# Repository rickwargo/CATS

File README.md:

#   C.A.T.S. 

## TODO
 - Module dependencies
 - Events
   - Event mapping that resides in systemSetup
   - Event dispatch that can deal with propagation 

### Enhancements
 - WiFi first then WiFiMulti to improve startup time
 - Pass different data based on event type
#### Done
 * [✓] Dynamically load and unload modules (low)

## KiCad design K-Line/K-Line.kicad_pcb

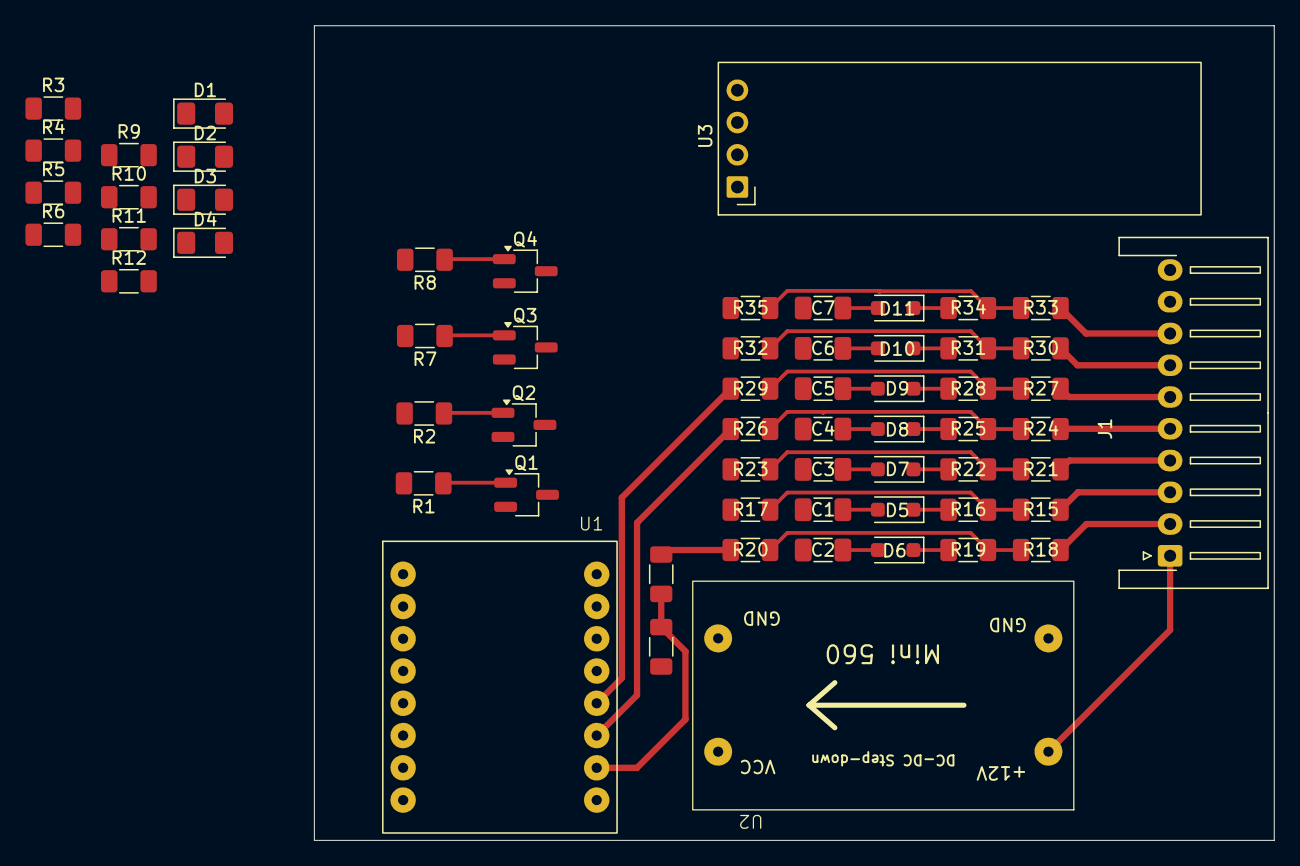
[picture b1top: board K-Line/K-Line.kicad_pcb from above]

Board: 2 copper layers, 75.6 x 64.1 mm, 61 parts (0 on the bottom side), 52 nets.

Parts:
C1, C2, C3, C4, C5, C6, C7: 100nF; C_1206_3216Metric_Pad1.33x1.80mm_HandSolder
D1, D3: Red LED; LED_1206_3216Metric_Pad1.42x1.75mm_HandSolder
D2, D4: LED; LED_1206_3216Metric_Pad1.42x1.75mm_HandSolder
D5, D6, D7, D8, D9, D10, D11: 3V3 0.5W; D_SOD-123F
J1: Conn_01x10_Pin; JST_XH_S10B-XH-A-1_1x10_P2.50mm_Horizontal
Q1, Q2, Q3, Q4: Q_NMOS_GSD; SC-59_Handsoldering
R1, R2, R7, R8: 100R; R_1206_3216Metric_Pad1.30x1.75mm_HandSolder
R3, R9: 220R; R_1206_3216Metric_Pad1.30x1.75mm_HandSolder
R4, R10: 510R; R_1206_3216Metric_Pad1.30x1.75mm_HandSolder
R5, R11, R14: 1K; R_1206_3216Metric_Pad1.30x1.75mm_HandSolder
R6, R12, R15, R16, R18, R19, R21, R22, R24, R25, R27, R28, R30, R31, R33, R34: 10K; R_1206_3216Metric_Pad1.30x1.75mm_HandSolder
R13: 4.7K; R_1206_3216Metric_Pad1.30x1.75mm_HandSolder
R17, R20, R23, R26, R29, R32, R35: 3K3; R_1206_3216Metric_Pad1.30x1.75mm_HandSolder
U1: ESP32-C3 SuperMini; ESP32-C3-SuperMini
U2: Mini-560
U3: ER_OLEDM0.91_1x-I2C

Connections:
+3V3: U2.4 (VCC), U3.2 (VCC)
+12V: J1.1, R4.1, R6.1, R10.1, R12.1, U2.1 (+12V)
/+12V SWITCHED: R13.2, R20.2
/+12V Switched Input/+12V_INPUT: J1.2, R18.1
/BRAKE: R29.2, U1.3 (GPIO7/SS)
/Brake Input/+12V_INPUT: J1.6, R27.1
/CLUTCH: R35.2, U1.6 (GPIO10)
/Clutch Input/+12V_INPUT: J1.8, R33.1
/HANDBRAKE: R26.2, U1.2 (GPIO6/MOSI)
/Handbrake Input/+12V_INPUT: J1.5, R24.1
/I2C_SCL: U1.8 (GPIO21/TX), U3.3 (SCL)
/I2C_SDA: U1.7 (GPIO20/RX), U3.4 (SDA)
/K-BUS: Q3.3 (D), Q4.3 (D), R10.2, R11.2, R12.2, R23.2
/K-BUS_RXD: R8.2, R9.2, U1.9 (A00)
/K-BUS_TXD: R7.2, U1.10 (A01)
/K-Bus Input/+12V_INPUT: J1.4, R21.1
/K-LINE: Q1.3 (D), Q2.3 (D), R4.2, R5.2, R6.2, R17.2
/K-LINE_RXD: R2.2, R3.2
/K-Line Input/+12V_INPUT: J1.3, R15.1
/PWR_MON: R13.1, R14.2, U1.1 (A05/MISO)
/REVERSE: R32.2, U1.5 (GPIO9/SCL)
/Reverse Input/+12V_INPUT: J1.7, R30.1
GND: C1.2, C2.2, C3.2, C4.2, C5.2, C6.2, C7.2, D1.1 (K), D2.1 (K), D3.1 (K), D4.1 (K), J1.10, Q1.2 (S), Q2.2 (S), Q3.2 (S), Q4.2 (S), R14.1, U2.2 (GNDPWR), U2.3 (GND), U3.1 (GND)
unnamed: D1.2 (A), R3.1
unnamed: D2.2 (A), R5.1
unnamed: D3.2 (A), R9.1
unnamed: D4.2 (A), R11.1
unnamed: C1.1, D5.2 (A)
unnamed: D5.1 (K), R16.2
unnamed: C2.1, D6.2 (A)
unnamed: D6.1 (K), R19.2
unnamed: C3.1, D7.2 (A)
unnamed: D7.1 (K), R22.2
unnamed: C4.1, D8.2 (A)
unnamed: D8.1 (K), R25.2
unnamed: C5.1, D9.2 (A)
unnamed: D9.1 (K), R28.2
unnamed: C6.1, D10.2 (A)
unnamed: D10.1 (K), R31.2
unnamed: C7.1, D11.2 (A)
unnamed: D11.1 (K), R34.2
unnamed: Q1.1 (G), R1.1
unnamed: Q2.1 (G), R2.1
unnamed: Q3.1 (G), R7.1
unnamed: Q4.1 (G), R8.1
unnamed: R15.2, R16.1, R17.1
unnamed: R18.2, R19.1, R20.1
unnamed: R21.2, R22.1, R23.1
unnamed: R24.2, R25.1, R26.1
unnamed: R27.2, R28.1, R29.1
unnamed: R30.2, R31.1, R32.1
unnamed: R33.2, R34.1, R35.1

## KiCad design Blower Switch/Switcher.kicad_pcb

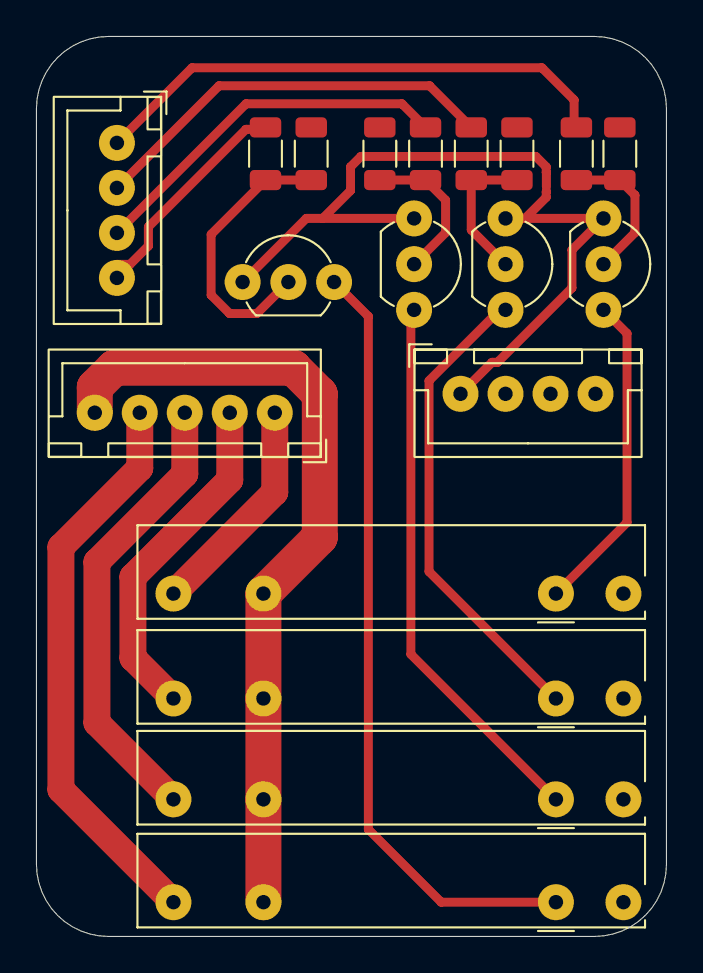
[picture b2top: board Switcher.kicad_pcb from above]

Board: 2 copper layers, 35.0 x 50.0 mm, 19 parts (0 on the bottom side), 19 nets.

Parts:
J1: Conn_01x04_Socket; JST_XH_B5B-XH-A_1x05_P2.50mm_Vertical
Q1, Q2, Q3, Q4: BC337; TO-92_Inline_Wide
R1, R2, R3, R4: 100K; R_1206_3216Metric
R5, R6, R7, R8: 2K2; R_1206_3216Metric
U1, U2, U3, U4: 34.81-7048; Finder_34.81
U5: GPIO Block; JST_XH_B4B-XH-A_1x04_P2.50mm_Vertical
U6: 3.3V Power; JST_XH_B4B-XH-A_1x04_P2.50mm_Vertical

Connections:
+3V3: Q1.1 (C), Q2.1 (C), Q3.1 (C), Q4.1 (C), U6.1 (3V3)
+12V: J1.5, U1.11, U2.11, U3.11, U4.11
/GPIO2: R5.1, U5.1 (GPIO2)
/GPIO3: R6.1, U5.2 (GPIO3)
/GPIO4: R7.1, U5.3 (GPIO4)
/GPIO21: R8.1, U5.4 (GPIO21)
/Select Speed 1: Q1.3 (E), U1.A1
/Select Speed 2: Q2.3 (E), U2.A1
/Select Speed 3: Q3.3 (E), U3.A1
/Select Speed 4: Q4.3 (E), U4.A1
/Speed 1: J1.1, U1.14
/Speed 1 Control: Q1.2 (B), R1.2, R5.2
/Speed 2: J1.2, U2.14
/Speed 2 Control: Q2.2 (B), R2.2, R6.2
/Speed 3: J1.3, U3.14
/Speed 3 Control: Q3.2 (B), R3.2, R7.2
/Speed 4: J1.4, U4.14
/Speed 4 Control: Q4.2 (B), R4.2, R8.2
GND: R1.1, R2.1, R3.1, R4.1, U1.A2, U2.A2, U3.A2, U4.A2, U6.2 (GND)

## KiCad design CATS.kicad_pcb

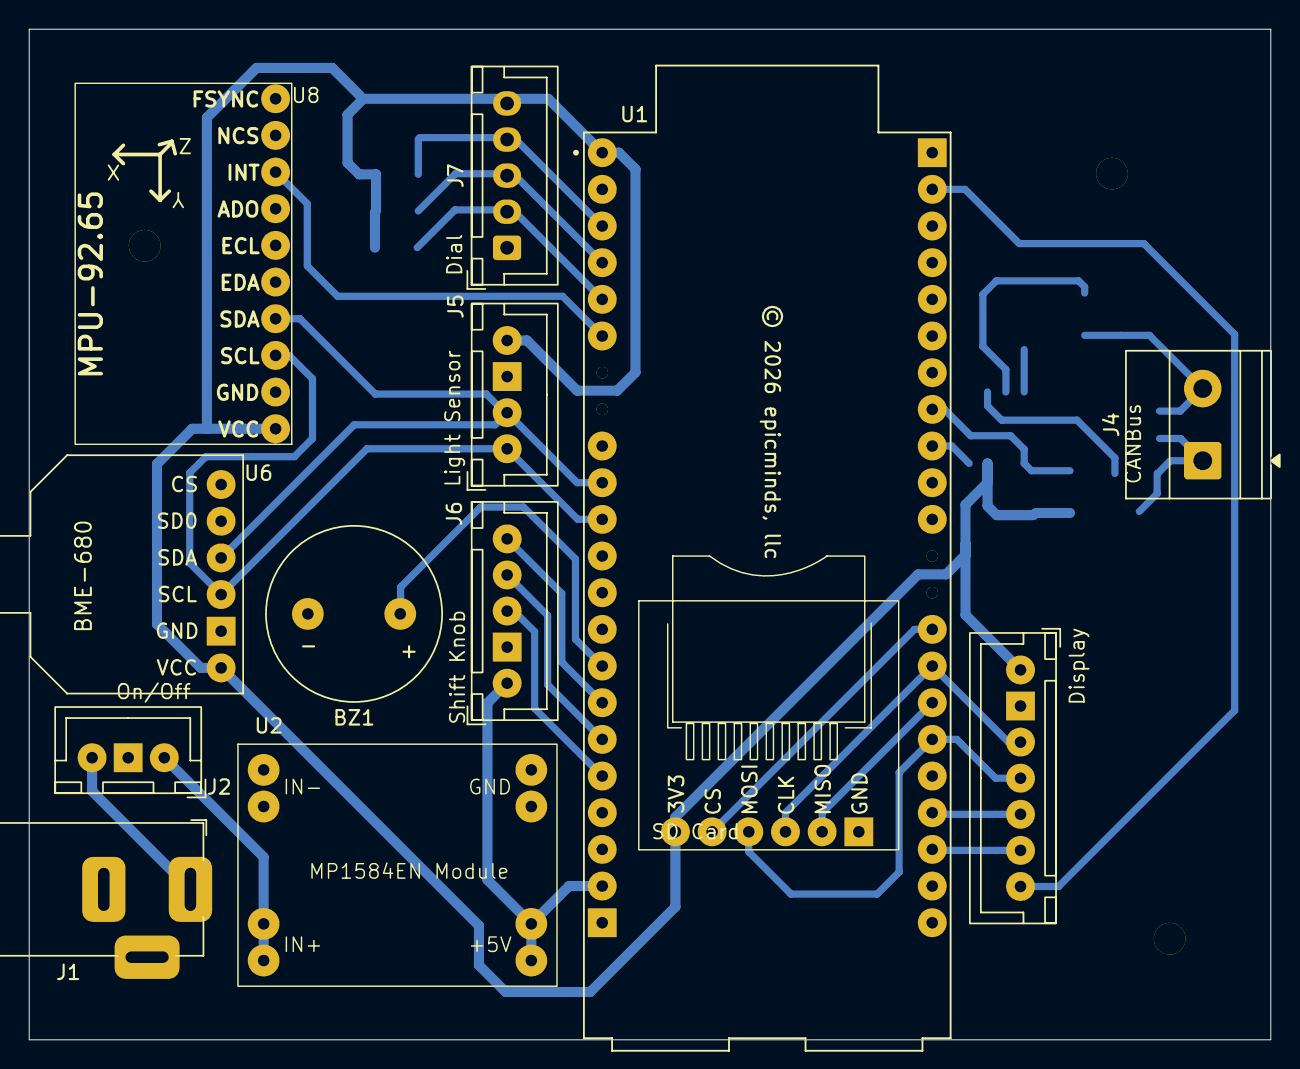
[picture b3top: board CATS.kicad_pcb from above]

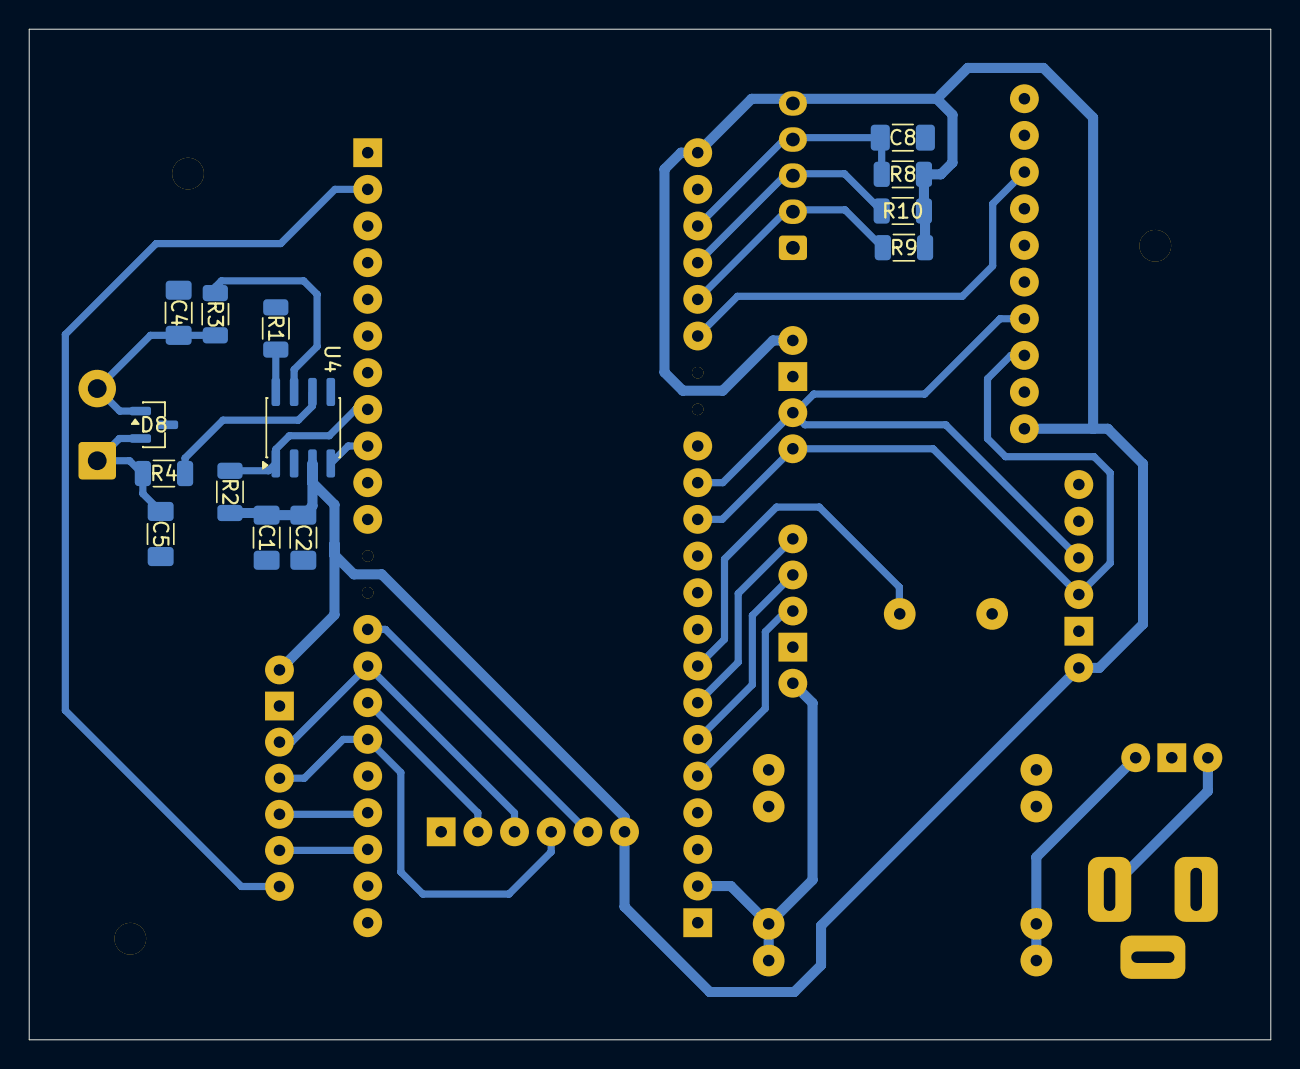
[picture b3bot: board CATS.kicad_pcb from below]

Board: 2 copper layers, 86.0 x 70.0 mm, 27 parts (14 on the bottom side), 29 nets.

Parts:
BZ1: Buzzer; Passive Buzzer
C1: 10uF; C_1206_3216Metric_Pad1.33x1.80mm_HandSolder
C2: 100nF; C_1206_3216Metric_Pad1.33x1.80mm_HandSolder
C4, C5: 47pF; C_1206_3216Metric_Pad1.33x1.80mm_HandSolder
C8: 0.1uF; C_1206_3216Metric_Pad1.33x1.80mm_HandSolder
D8: PESD5V0L2BT; SOT-23
J1: Barrel_Jack; BarrelJack_Horizontal
J2: Conn_01x03; JST_XH_B3B-XH-A_1x03_P2.50mm_Vertical
J3: Conn_01x07; JST_XH_B7B-XH-A_1x07_P2.50mm_Vertical
J4: Conn_01x02; TerminalBlock_Phoenix_MKDS-1,5-2_1x02_P5.00mm_Horizontal
J5: Conn_01x04; JST_XH_B4B-XH-A_1x04_P2.50mm_Vertical
J6, J7: Conn_01x05; JST_XH_B5B-XH-A_1x05_P2.50mm_Vertical
R1: 0R; R_1206_3216Metric
R2: 4K7; R_1206_3216Metric
R3, R4: 10R; R_1206_3216Metric
R8, R9, R10: 10K; R_1206_3216Metric
U1: ESP32-S3-DevKitM-1-N8
U2: MP1584EN; MP1584EN_DCDC_THT_Module
U4: SN65HVD230; SOIC-8_3.9x4.9mm_P1.27mm
U5: Micro_SD_Card
U6: BME-680
U8: MPU-6050; MPU-6500

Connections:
+3.3V: C1.1, C2.1, J3.1, J5.4, J7.5, R2.2, R8.1, R9.1, R10.1, U1.J1_1 (3V3), U4.3 (VCC), U5.1 (3V3), U6.1 (VCC), U8.1 (VCC)
+5V: J6.1, U1.J1_21 (5V0), U2.4 (VOUT)
+12V: J2.1, U2.1 (VIN)
/+12V_IN: J1.1 (+12V), J2.3
/CAN RS: R1.2, U4.8 (Rs)
/CANBUS+: R3.1, U4.7 (CANH)
/CANBUS-: R4.2, U4.6 (CANL)
/CB+EXT: C4.2, D8.1 (A1), J4.2, R3.2
/CB-EXT: C5.1, D8.2 (A2), J4.1, R4.1
BUTTON1: C8.1, J7.4, R8.2, U1.J1_3 (GPIO1)
BUZZER: BZ1.1 (+), U1.J1_15 (GPIO13)
CAN D: R2.1, U1.J3_8 (GPIO41), U4.1 (D)
CAN R: U1.J3_9 (GPIO40), U4.4 (R)
ENCODER A: J7.3, R10.2, U1.J1_4 (GPIO2)
ENCODER B: J7.2, R9.2, U1.J1_5 (GPIO3)
FSPI CLK: J3.3, U1.J3_15 (GPIO34), U5.4 (CLK)
FSPI MISO: U1.J3_16 (GPIO33), U5.5 (MISO)
FSPI MOSI: J3.4, U1.J3_17 (GPIO26), U5.3 (MOSI)
GND: BZ1.2 (-), C1.2, C2.2, C4.1, C5.2, C8.2, D8.3 (common), J1.2 (GND), J2.2, J3.2, J5.3, J6.2, J7.1, R1.1, U1.J1_22 (GND_J1_22), U1.J3_1 (GND_J3_1), U2.2 (GND), U2.3 (GND), U4.2 (GND), U5.6 (GND), U6.2 (GND), U8.2 (GND)
HAPTIC1: J6.5, U1.J1_16 (GPIO14)
HAPTIC2: J6.4, U1.J1_17 (GPIO15)
LIGHTS: J6.3, U1.J1_18 (GPIO16)
MPU INT: U1.J1_6 (GPIO4), U8.8 (INT)
RESET: J3.7, U1.J3_2 (RST)
SCL: J5.1, U1.J1_11 (GPIO9), U6.3 (SCL), U8.3 (SCL)
SD CS: U1.J3_14 (GPIO35), U5.2 (~CS)
SDA: J5.2, U1.J1_10 (GPIO8), U6.4 (SDA), U8.4 (SDA)
TFT CS: J3.6, U1.J3_20 (GPIO19)
TFT DC: J3.5, U1.J3_19 (GPIO20)

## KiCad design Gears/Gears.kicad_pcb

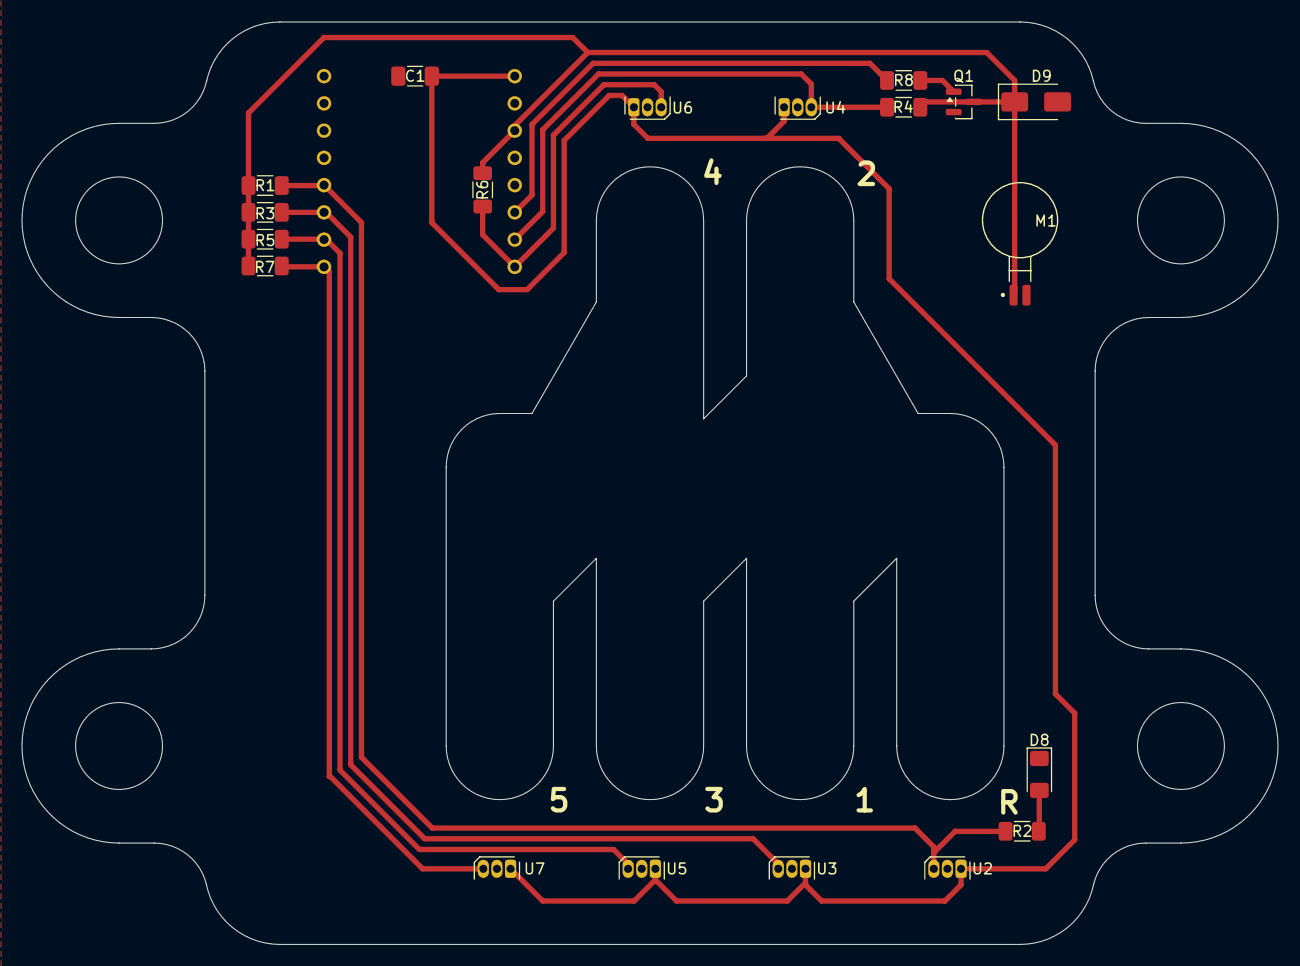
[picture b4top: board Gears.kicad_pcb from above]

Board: 2 copper layers, 117.1 x 86.0 mm, 20 parts (1 on the bottom side), 12 nets.

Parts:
C1: 0.1uF; C_1206_3216Metric_Pad1.33x1.80mm_HandSolder
D8: LED; LED_1206_3216Metric_Pad1.42x1.75mm_HandSolder
D9: SS12; D_SMA
M1: C0720B001F; XDCR_C0720B001F
Q1: BC817; SOT-23
R1, R3, R4, R5, R6, R7: 10K; R_1206_3216Metric_Pad1.30x1.75mm_HandSolder
R2: 220R; R_1206_3216Metric_Pad1.30x1.75mm_HandSolder
R8: 1K; R_1206_3216Metric_Pad1.30x1.75mm_HandSolder
U1: ESP32-C3-OLED; MODULE_ESP32-C3_OLED
U2, U3, U4, U5, U6, U7: A3314; TO-92S

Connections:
1ST_GEAR: R3.1, U1.5 (GPIO5), U3.3 (V_{OUT})
2ND_GEAR: R4.1, U1.1 (GPIO1), U4.3 (V_{OUT})
3RD_GEAR: R5.1, U1.4 (GPIO4), U5.3 (V_{OUT})
4TH_GEAR: R6.1, U1.0 (GPIO0), U6.3 (V_{OUT})
5TH_GEAR: R7.1, U1.3 (GPIO3), U7.3 (V_{OUT})
+3.3V: D9.1 (K), M1.1 (V+), Q1.3 (C), R1.1, R3.2, R4.2, R5.2, R6.2, R7.2, U1.3.3 (3V3)
+5V: C1.1, U1.5V, U2.1 (V_{CC}), U3.1 (V_{CC}), U4.1 (V_{CC}), U5.1 (V_{CC}), U6.1 (V_{CC}), U7.1 (V_{CC})
GND: C1.2, D8.1 (K), D9.2 (A), M1.2 (V-), Q1.2 (E), U1.G (GND), U2.2 (GND), U3.2 (GND), U4.2 (GND), U5.2 (GND), U6.2 (GND), U7.2 (GND)
HAPTIC: R8.1, U1.2 (GPIO2)
Haptic_Trigger: Q1.1 (B), R8.2
REVERSE: R1.2, R2.2, U1.6 (GPIO6), U2.3 (V_{OUT})
Reverse_Light: D8.2 (A), R2.1

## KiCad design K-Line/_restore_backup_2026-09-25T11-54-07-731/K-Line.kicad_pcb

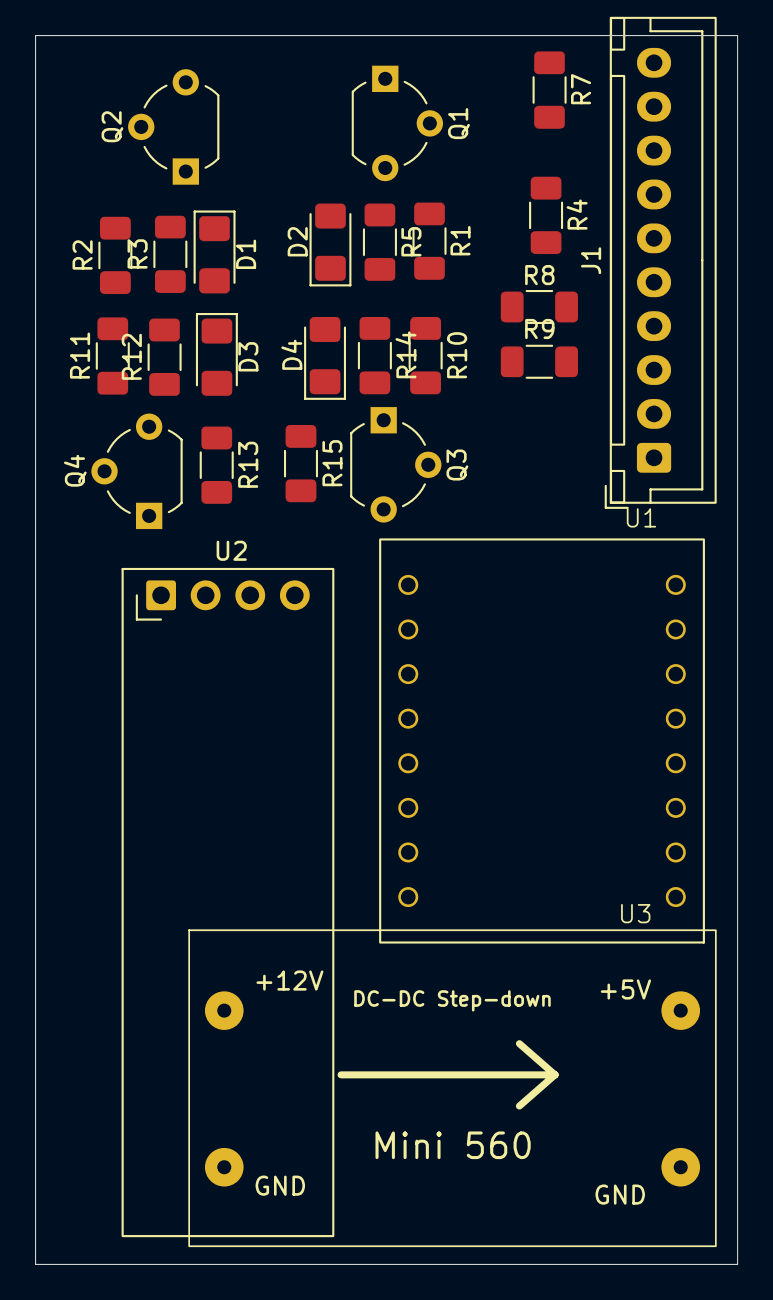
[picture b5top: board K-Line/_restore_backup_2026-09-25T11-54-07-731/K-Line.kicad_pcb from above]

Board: 2 copper layers, 40.0 x 70.0 mm, 26 parts (0 on the bottom side), 23 nets, no tracks yet.

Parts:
D1, D3: Red LED; LED_1206_3216Metric_Pad1.42x1.75mm_HandSolder
D2, D4: LED; LED_1206_3216Metric_Pad1.42x1.75mm_HandSolder
J1: Conn_01x10_Pin; JST_XH_B10B-XH-A_1x10_P2.50mm_Vertical
Q1, Q2, Q3, Q4: BC547; TO-92_Wide
R1, R2, R5, R9, R10, R11, R14: 1K; R_1206_3216Metric_Pad1.30x1.75mm_HandSolder
R3, R12: 220R; R_1206_3216Metric_Pad1.30x1.75mm_HandSolder
R4, R13: 510R; R_1206_3216Metric_Pad1.30x1.75mm_HandSolder
R7, R15: 10K; R_1206_3216Metric_Pad1.30x1.75mm_HandSolder
R8: 4.7K; R_1206_3216Metric_Pad1.30x1.75mm_HandSolder
U1: ESP32-C3 SuperMini; ESP32-C3-SuperMini
U2: ER_OLEDM0.91_1x-I2C
U3: Mini-560

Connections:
+3V3: U2.2 (VCC), U3.4 (VCC)
+12V: J1.1, R4.1, R7.1, R13.1, R15.1, U3.1 (+12V)
/+12V SWITCHED: J1.2, R8.2
/BRAKE: J1.6, U1.3 (GPIO7/SS)
/CLUTCH: J1.8, U1.6 (GPIO10)
/HANDBRAKE: J1.5, U1.2 (GPIO6/MOSI)
/I2C_SCL: U1.8 (GPIO21/TX), U2.3 (SCL)
/I2C_SDA: U1.7 (GPIO20/RX), U2.4 (SDA)
/K-BUS: J1.4, Q3.1 (C), Q4.1 (C), R13.2, R14.2, R15.2
/K-BUS_RXD: R11.2, R12.2, U1.10 (A01)
/K-LINE: J1.3, Q1.1 (C), Q2.1 (C), R4.2, R5.2, R7.2
/K-LINE_RXD: R2.2, R3.2
/PWR_MON: R8.1, R9.2, U1.1 (A05/MISO)
/REVERSE: J1.7, U1.5 (GPIO9/SCL)
GND: D1.1 (K), D2.1 (K), D3.1 (K), D4.1 (K), J1.10, Q1.3 (E), Q2.3 (E), Q3.3 (E), Q4.3 (E), R9.1, U2.1 (GND), U3.2 (GNDPWR), U3.3 (GND)
unnamed: D1.2 (A), R3.1
unnamed: D2.2 (A), R5.1
unnamed: D3.2 (A), R12.1
unnamed: D4.2 (A), R14.1
unnamed: Q1.2 (B), R1.1
unnamed: Q2.2 (B), R2.1
unnamed: Q3.2 (B), R10.1
unnamed: Q4.2 (B), R11.1

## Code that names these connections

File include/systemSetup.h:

#pragma once

#define SHIFTER_UPDATES_PER_SECOND  30

#define VSPI_CLK                    2
#define VSPI_MISO                   4
#define VSPI_MOSI                   16
#define VSPI_FREQUENCY              10000000

#define VSPI_TFT_CS                 14
#define VSPI_TFT_DC                 27
#define VSPI_TFT_RST                12

#define FILE_BASE_NAME              "cats"
#define SD_CS                       15
#define SD_CLK                      VSPI_CLK
#define SD_MISO                     VSPI_MISO
#define SD_MOSI                     VSPI_MOSI

// #define IMU_INTERRUPT_PIN           19

#define ROTARY_BUTTON_PIN           36
#define ENCODER_A                   34 // Encoder CLK
#define ENCODER_B                   39 // Encoder DT
#define ENCODER_DEFAULT_STEPS       4

#define HAPTIC_PIN_1                32
#define HAPTIC_PIN_2                33
#define SHIFTER_PIN                 25

#define BUZZER_PIN                  17

#define CAN_TX_PIN                  ((gpio_num_t)5)
#define CAN_RX_PIN                  ((gpio_num_t)18)
#define CANBUS_SPEED                500

#define I2C_SDA                     22
#define I2C_SCL                     23
#define I2C_BUS_FREQUENCY           400000

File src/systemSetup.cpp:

#include "systemSetup.h"
#include "ModuleRegistry.h"

#include "SystemModule.h"
#ifdef UI_DISPLAY
#include "DisplayModule.h"
#endif
#ifdef NETWORKING
#include "NetworkModule.h"
#if defined(NETWORK_TIME)
#include "TimeModule.h"
#endif
#endif
#ifdef CANBUS
#include "CANBusModule.h"
#endif
#ifdef BUTTON
#include "ButtonModule.h"
#endif
#ifdef BUZZER_SOUND
#include "BuzzerModule.h"
#endif
#ifdef ENCODER
#include "EncoderModule.h"
#endif
#ifdef LIGHT_LEVEL_SENSOR
#include "LightLevelModule.h"
#endif
#if defined(SHIFTER_KNOB) && defined(HAPTIC)
#include "HapticModule.h"
#endif
#if defined(SHIFTER_KNOB) && (defined(HAPTIC) || defined(FAST_LED))
#include "ShifterModule.h"
#endif
#ifdef ENVIRONMENT_SENSOR
#include "EnvironmentModule.h"
#endif
#ifdef IMU_SENSOR
#include "IMUModule.h"
#endif
#ifdef STORAGE
#include "StorageModule.h"
#endif
#if defined(NETWORKING) && defined(OTA_UPDATE)
#include "OTAUpdateModule.h"
#endif

#ifdef UI_DISPLAY
#include "face/FaceManager.h"
#endif
#if defined(UI_DISPLAY) && defined(NETWORKING) && defined(NETWORK_TIME)
#include "face/ClockFace.h"
#endif
#if defined(UI_DISPLAY) && defined(ENVIRONMENT_SENSOR)
#include "face/TemperatureFace.h"
#include "face/HumidityFace.h"
#include "face/IAQFace.h"
#include "face/PressureFace.h"
#endif
#if defined(UI_DISPLAY) && defined(LIGHT_LEVEL_SENSOR)
#include "face/LightLevelFace.h"
#endif
#if defined(UI_DISPLAY) && defined(IMU_SENSOR)
#include "face/IMUFace.h"
#include "face/DGFace.h"
#include "face/AutoFace.h"
#endif
#if defined(UI_DISPLAY) && (defined(LIGHT_LEVEL_SENSOR) || defined(IMU_SENSOR) || defined(ENVIRONMENT_SENSOR))
#include "face/MeasuresFace.h"
#endif

void loadModules()
{
    ModuleRegistry& registry = ModuleRegistry::instance();

    // Load order is significant - specify dependent modules first
    static SystemModule systemModule("System Handler");
    registry.registerModule(systemModule);

#ifdef NETWORKING
    static NetworkModule networkModule("Network Overlord");
#if defined(NETWORK_TIME)
    static TimeModule timeModule("Time Syncer");
#endif
#if defined(NETWORKING) && defined(OTA_UPDATE)
    static OTAUpdateModule otaUpdateModule("OTA Updates");
#endif
#endif

#ifdef UI_DISPLAY
    static DisplayModule displayModule("Round Display");
    static FaceManager faceManager("Face Manager", 1000);   // Must be loaded prior to loading faces
#if defined(NETWORK_TIME)
    static ClockFace clockFace("Clock", 500);
#endif
#ifdef ENVIRONMENT_SENSOR
    static TemperatureFace temperatureFace("Inside Temperature");
    static HumidityFace humidityFace("Humidity");
    static IAQFace iaqFace("IAQ");
    static PressureFace pressureFace("Pressure");
#endif
#ifdef LIGHT_LEVEL_SENSOR
    static LightLevelFace lightLevelFace("Light Level");
#endif
#if defined(LIGHT_LEVEL_SENSOR) || defined(IMU_SENSOR) || defined(ENVIRONMENT_SENSOR)
    static MeasuresFace measuresFace("Measures");
#endif
#ifdef IMU_SENSOR
    static DGFace dgFace("DG", 50);
    static AutoFace autoFace("Auto", 0);
    static IMUFace imuFace("Y/P/R");
#endif
#endif

#if defined(SHIFTER_KNOB)
    static ShifterModule shifterModule("Shifter LED", SHIFTER_PIN);
#ifdef HAPTIC
    static HapticModule hapticForwardModule("Haptic Feedback Forward", HAPTIC_PIN_1);
    // static HapticModule hapticReverseModule("Haptic Feedback Reverse", HAPTIC_PIN_2);
#endif
#endif

#ifdef CANBUS
    static CANBusModule canBusModule("CAN Bus Transceiver", CAN_TX_PIN, CAN_RX_PIN, CANBUS_SPEED);
#endif
#ifdef BUTTON
    static ButtonModule buttonModule("Rotary Button", ROTARY_BUTTON_PIN);
#endif
#ifdef BUZZER_SOUND
    static BuzzerModule buzzerModule("Main Buzzer", BUZZER_PIN);
#endif
#ifdef ENCODER
    static EncoderModule encoderModule("Rotary Encoder", ENCODER_A, ENCODER_B, ENCODER_DEFAULT_STEPS);
#endif
#ifdef LIGHT_LEVEL_SENSOR
    static LightLevelModule lightLevelModule("Light Level Sensor", 2000);
#endif
#ifdef ENVIRONMENT_SENSOR
    static EnvironmentModule environmentModule("Environment Sensor", (unsigned int)round(1/SAMPLE_RATE));
#endif
#ifdef IMU_SENSOR
    static IMUModule imuModule("Inertial Measurement Unit", 50);
#endif
#ifdef STORAGE
    static StorageModule storageModule("SD Card Storage");
#endif

#ifdef UI_DISPLAY
    registry.registerModule(displayModule);
#endif
#ifdef NETWORKING
    registry.registerModule(networkModule);
#endif
#if defined(NETWORKING) && defined(NETWORK_TIME)
    registry.registerModule(timeModule);
#endif
#ifdef CANBUS
    registry.registerModule(canBusModule);
#endif
#ifdef BUTTON
    registry.registerModule(buttonModule);
#endif
#ifdef BUZZER_SOUND
    registry.registerModule(buzzerModule);
#endif
#ifdef ENCODER
    registry.registerModule(encoderModule);
#endif
#ifdef LIGHT_LEVEL_SENSOR
    registry.registerModule(lightLevelModule);
#endif
#ifdef HAPTIC
    registry.registerModule(hapticForwardModule);
    // registry.registerModule(hapticReverseModule);
#endif
#ifdef SHIFTER_KNOB
    registry.registerModule(shifterModule);
#endif
#ifdef ENVIRONMENT_SENSOR
    registry.registerModule(environmentModule);
#endif
#ifdef IMU_SENSOR
    registry.registerModule(imuModule);
#endif
#ifdef STORAGE
    registry.registerModule(storageModule);
#endif
#if defined(NETWORKING) && defined(OTA_UPDATE)
    registry.registerModule(otaUpdateModule);
#endif

#ifdef UI_DISPLAY
    registry.registerModule(faceManager);
#if defined(NETWORKING) && defined(NETWORK_TIME)
    registry.registerModule(clockFace);
#endif
#if defined(IMU_SENSOR)
    registry.registerModule(dgFace);
    registry.registerModule(autoFace);
    registry.registerModule(imuFace);
#endif
#if defined(ENVIRONMENT_SENSOR)
    registry.registerModule(temperatureFace);
    registry.registerModule(humidityFace);
    registry.registerModule(iaqFace);
    registry.registerModule(pressureFace);
#endif
#if defined(LIGHT_LEVEL_SENSOR)
    registry.registerModule(lightLevelFace);
#endif
#if defined(LIGHT_LEVEL_SENSOR) || defined(IMU_SENSOR) || defined(ENVIRONMENT_SENSOR)
    registry.registerModule(measuresFace);
#endif
#endif
}

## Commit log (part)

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2026-06-11 Updated to using more generic measures to display one or more values
2026-06-11 Add .DS_Store to .gitignore
2026-06-12 Added directional gyro visualization as a new face
2026-06-12 UI fixes/changes
2026-06-12 rm old files
2026-06-12 Add driving car parallax "face"
2026-06-12 Update units to use some special chars

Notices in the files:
CATS.kicad_pcb:
© 2026 epicminds, llc
